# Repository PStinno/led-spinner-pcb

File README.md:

# led-spinner-pcb
My first two layer PCB, spinning LED effect with no micro-controller or code.

The circuit consists of two 4017 decade counters, connected together to create sixteen sequential outputs. The outputs progress on each clock cycle and loop back to the beginning when the end is reached. Each output is connected to an LED on the perimeter of the PCB. The clock input is connected to a 555 timer IC in an astable configuration. This generates a continous square wave, causing the progression of the outputs and the spinning effect. The momentary push button completes the circuit, so it is only powered when the button is held down.

[![CC BY-SA 4.0][cc-by-sa-image]][cc-by-sa]

[cc-by-sa]: http://creativecommons.org/licenses/by-sa/4.0/
[cc-by-sa-image]: https://licensebuttons.net/l/by-sa/4.0/88x31.png
[cc-by-sa-shield]: https://img.shields.io/badge/License-CC%20BY--SA%204.0-lightgrey.svg

This work is licensed under a [Creative Commons Attribution-ShareAlike 4.0 International License][cc-by-sa].

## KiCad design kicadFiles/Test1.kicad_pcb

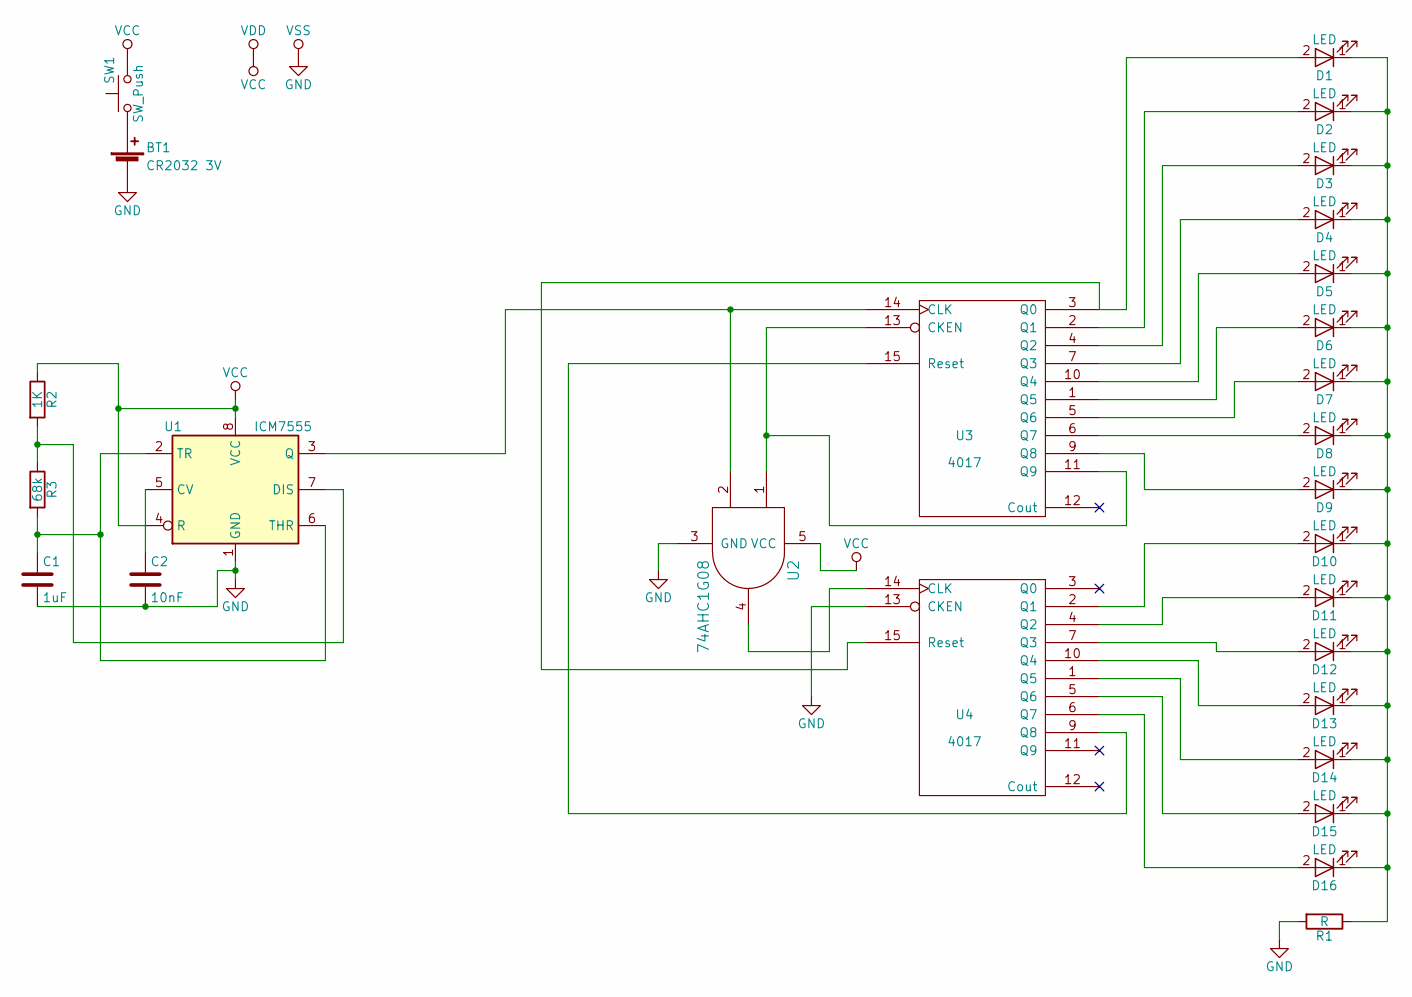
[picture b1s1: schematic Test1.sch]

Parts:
BT1: CR2032 3V; MPD_BA2032SM
C1: 1uF; C_0805
C2: 10nF; C_0805
D1, D2, D3, D4, D5, D6, D7, D8, D9, D10, D11, D12, D13, D14, D15, D16: LED; LED_0805
R1: R; R_0805
R2: 1K; R_0805
R3: 68k; R_0805
SW1: SW_Push; SW_SPST_PTS645
U1: ICM7555; SOIC-8_3.9x4.9mm_Pitch1.27mm
U2: 74AHC1G08; SOT-353_SC-70-5
U3, U4: 4017; SOIC-16_3.9x9.9mm_Pitch1.27mm

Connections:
GND: BT1.2 (-), C1.2, C2.2, R1.2, U1.1 (GND), U2.3 (GND), U3.8 (VSS), U4.8 (VSS), U4.13 (CKEN)
unnamed: BT1.1 (+), SW1.1
unnamed: C1.1, R3.2, U1.2 (TR), U1.6 (THR)
unnamed: C2.1, U1.5 (CV)
unnamed: D1.1 (K), D2.1 (K), D3.1 (K), D4.1 (K), D5.1 (K), D6.1 (K), D7.1 (K), D8.1 (K), D9.1 (K), D10.1 (K), D11.1 (K), D12.1 (K), D13.1 (K), D14.1 (K), D15.1 (K), D16.1 (K), R1.1
unnamed: D1.2 (A), U3.3 (Q0), U4.15 (Reset)
unnamed: D2.2 (A), U3.2 (Q1)
unnamed: D3.2 (A), U3.4 (Q2)
unnamed: D4.2 (A), U3.7 (Q3)
unnamed: D5.2 (A), U3.10 (Q4)
unnamed: D6.2 (A), U3.1 (Q5)
unnamed: D7.2 (A), U3.5 (Q6)
unnamed: D8.2 (A), U3.6 (Q7)
unnamed: D9.2 (A), U3.9 (Q8)
unnamed: D10.2 (A), U4.2 (Q1)
unnamed: D11.2 (A), U4.4 (Q2)
unnamed: D12.2 (A), U4.7 (Q3)
unnamed: D13.2 (A), U4.10 (Q4)
unnamed: D14.2 (A), U4.1 (Q5)
unnamed: D15.2 (A), U4.5 (Q6)
unnamed: D16.2 (A), U4.6 (Q7)
unnamed: R2.2, R3.1, U1.7 (DIS)
unnamed: U1.3 (Q), U2.2, U3.14 (CLK)
unnamed: U2.1, U3.11 (Q9), U3.13 (CKEN)
unnamed: U2.4, U4.14 (CLK)
unnamed: U3.15 (Reset), U4.9 (Q8)
VCC: R2.1, SW1.2, U1.4 (R), U1.8 (VCC), U2.5 (VCC), U3.16 (VDD), U4.16 (VDD)

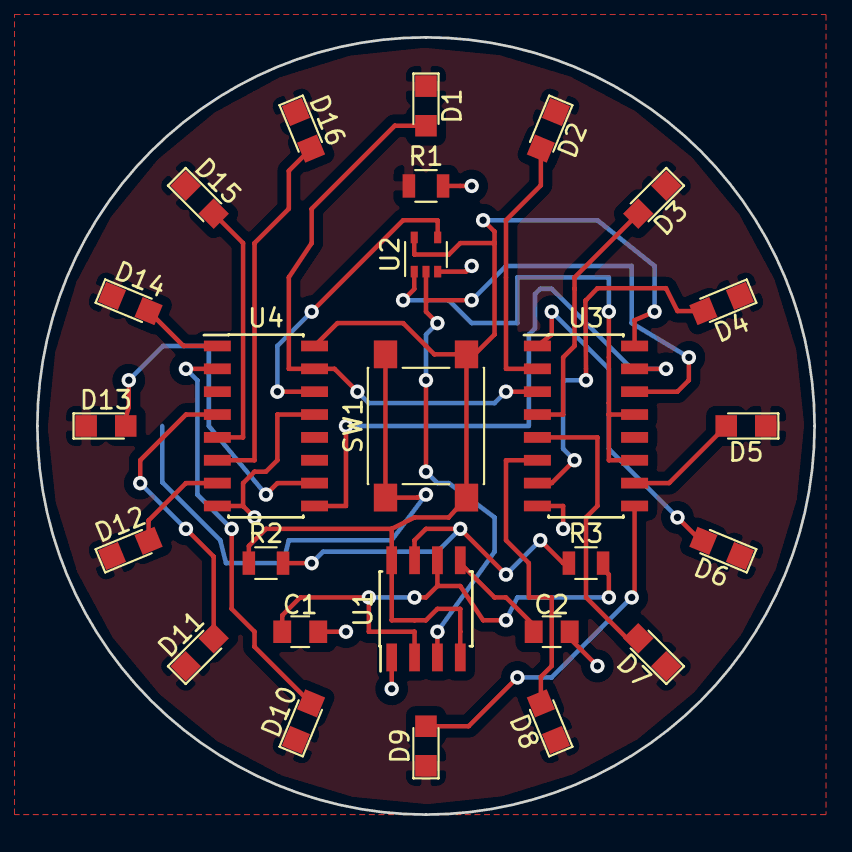
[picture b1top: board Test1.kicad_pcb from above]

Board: 2 copper layers, 43.2 x 43.2 mm, 27 parts (1 on the bottom side), 27 nets.

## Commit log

2019-03-22 Update README, add basic circuit description
2019-03-22 Create images directory
2019-03-22 Upload images of project
2019-03-22 Add images to README
2019-03-22 Add kicad design files
2019-03-22 Update circuit description
2022-04-14 Added license file
